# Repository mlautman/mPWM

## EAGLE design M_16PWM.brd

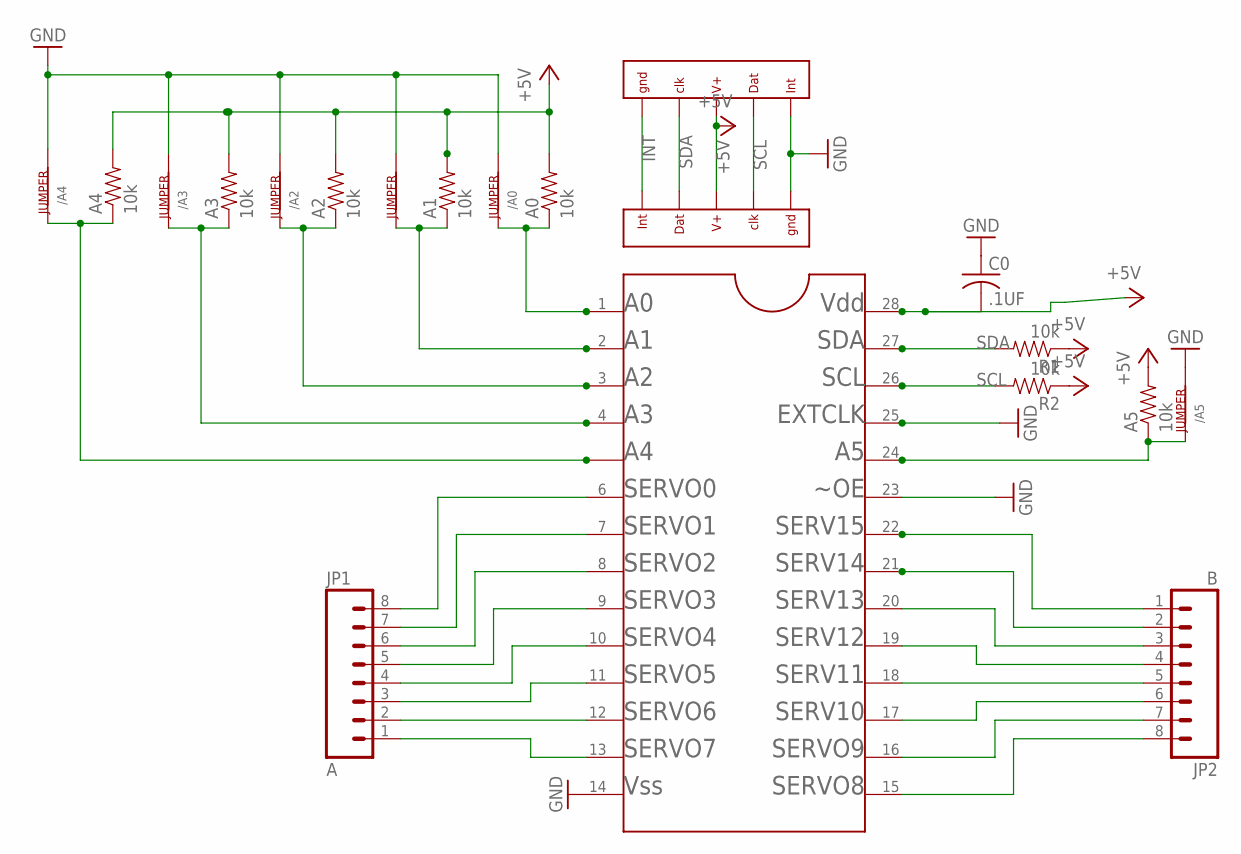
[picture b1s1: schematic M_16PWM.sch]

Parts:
/A0, /A1, /A2, /A3, /A4, /A5: JUMPER
A0, A1, A2, A3, A4, A5: 10k; 0402-RES
C0: .1UF; C0603
JP1: A; 1X08
JP2: B; 1X08
R1, R2: 10k; 0402-RES
U$1: PCA9685PW; TSSOP28
U$2, U$3: 050-5

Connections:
+5V: A0.2, A1.2, A2.2, A3.2, A4.2, A5.2, C0.2, R1.1, R2.1, U$1.28, U$2.P$3, U$3.P$3
GND: /A0.2, /A1.2, /A2.2, /A3.2, /A4.2, /A5.2, C0.1, U$1.14, U$1.23, U$1.25, U$2.P$5, U$3.P$1
INT: U$2.P$1, U$3.P$5
unnamed: JP1.8, U$1.6
unnamed: JP1.7, U$1.7
unnamed: JP1.6, U$1.8
unnamed: JP1.5, U$1.9
unnamed: JP1.4, U$1.10
unnamed: JP1.3, U$1.11
unnamed: JP1.2, U$1.12
unnamed: JP1.1, U$1.13
unnamed: /A5.1, A5.1, U$1.24
unnamed: JP2.8, U$1.15
unnamed: JP2.7, U$1.16
unnamed: JP2.6, U$1.17
unnamed: JP2.5, U$1.18
unnamed: JP2.4, U$1.19
unnamed: JP2.3, U$1.20
unnamed: JP2.1, U$1.22
unnamed: JP2.2, U$1.21
unnamed: /A0.1, A0.1, U$1.1
unnamed: /A4.1, A4.1, U$1.5
unnamed: /A2.1, A2.1, U$1.3
unnamed: /A3.1, A3.1, U$1.4
unnamed: /A1.1, A1.1, U$1.2
SCL: R2.2, U$1.26, U$2.P$4, U$3.P$2
SDA: R1.2, U$1.27, U$2.P$2, U$3.P$4

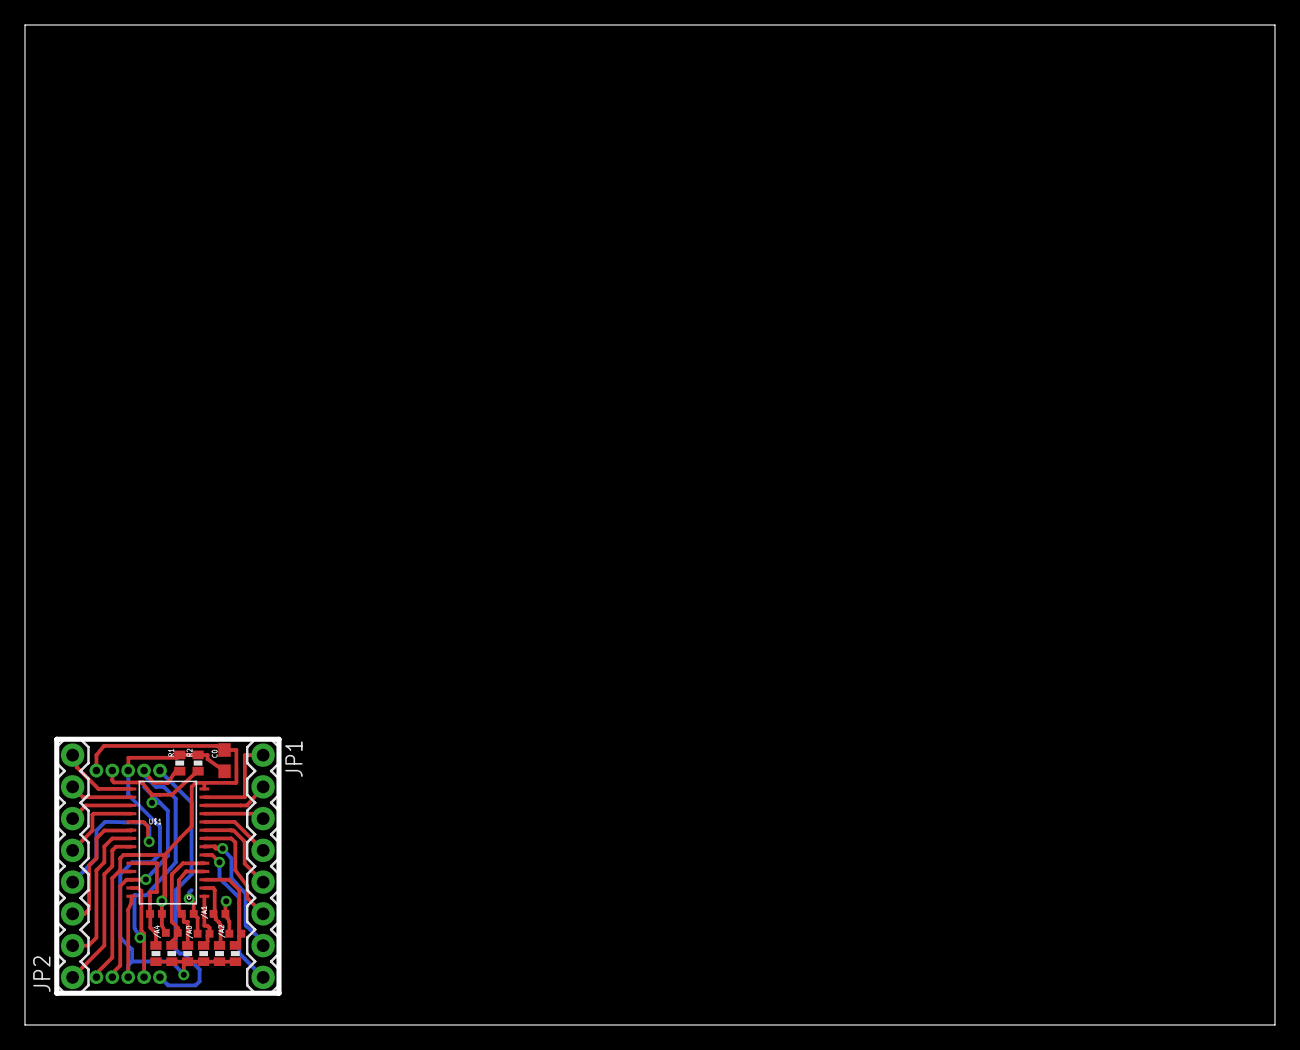
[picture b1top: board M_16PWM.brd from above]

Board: 2 copper layers, 99.6 x 79.6 mm, 20 parts (0 on the bottom side), 27 nets.

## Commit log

2014-03-28 uploading mPWM code for the M4 to the internet
2016-04-14 pushing mPWM to git
2016-04-14 adding board and schematic files
2016-04-14 adding requisite m_bus library

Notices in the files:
parts and their libraries:
SparkFun-DigitalIC: Licensing: CC v3.0 Share-Alike You are welcome to use this library for commercial purposes.
